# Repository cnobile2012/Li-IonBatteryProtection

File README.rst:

*************************
Li-Ion Battery Protection
*************************
The MIT License (MIT)

This is an electronics project to help protect Li-Ion batteries and the
circuits they are used in. The circuit will work with two to four cells and
protects the battery at the cell level. Any one cell that goes below the
recomended level will cause the entire curcuit to shut down.

=======
LTspice
=======

Spice files for testing the circuit virtually.

Truth Table One: Battery Voltage Normal

+-------+-------+-------+-------+-------+
| U1/U3 | Q1/Q2 | U2/U4 |  Q3   |  Q4   |
+=======+=======+=======+=======+=======+
|  HI   |  LOW  |  LOW  |  HI   |  LOW  |
+-------+-------+-------+-------+-------+
|  N/A  |  ON   |  ON   |  OFF  |  ON   |
+-------+-------+-------+-------+-------+

Truth Table Two: Battery Voltage Below Normal

+-------+-------+-------+-------+-------+
| U1/U3 | Q1/Q2 | U2/U4 |  Q3   |  Q4   |
+=======+=======+=======+=======+=======+
|  LOW  |  HI   |  HI   |  LOW  |  HI   |
+-------+-------+-------+-------+-------+
|  N/A  |  OFF  |  OFF  |  ON   |  OFF  |
+-------+-------+-------+-------+-------+

=====
KiCAD
=====

KiCAD files of the schematic and PCB.

Feel free to contact me at: carl dot nobile at gmail.com

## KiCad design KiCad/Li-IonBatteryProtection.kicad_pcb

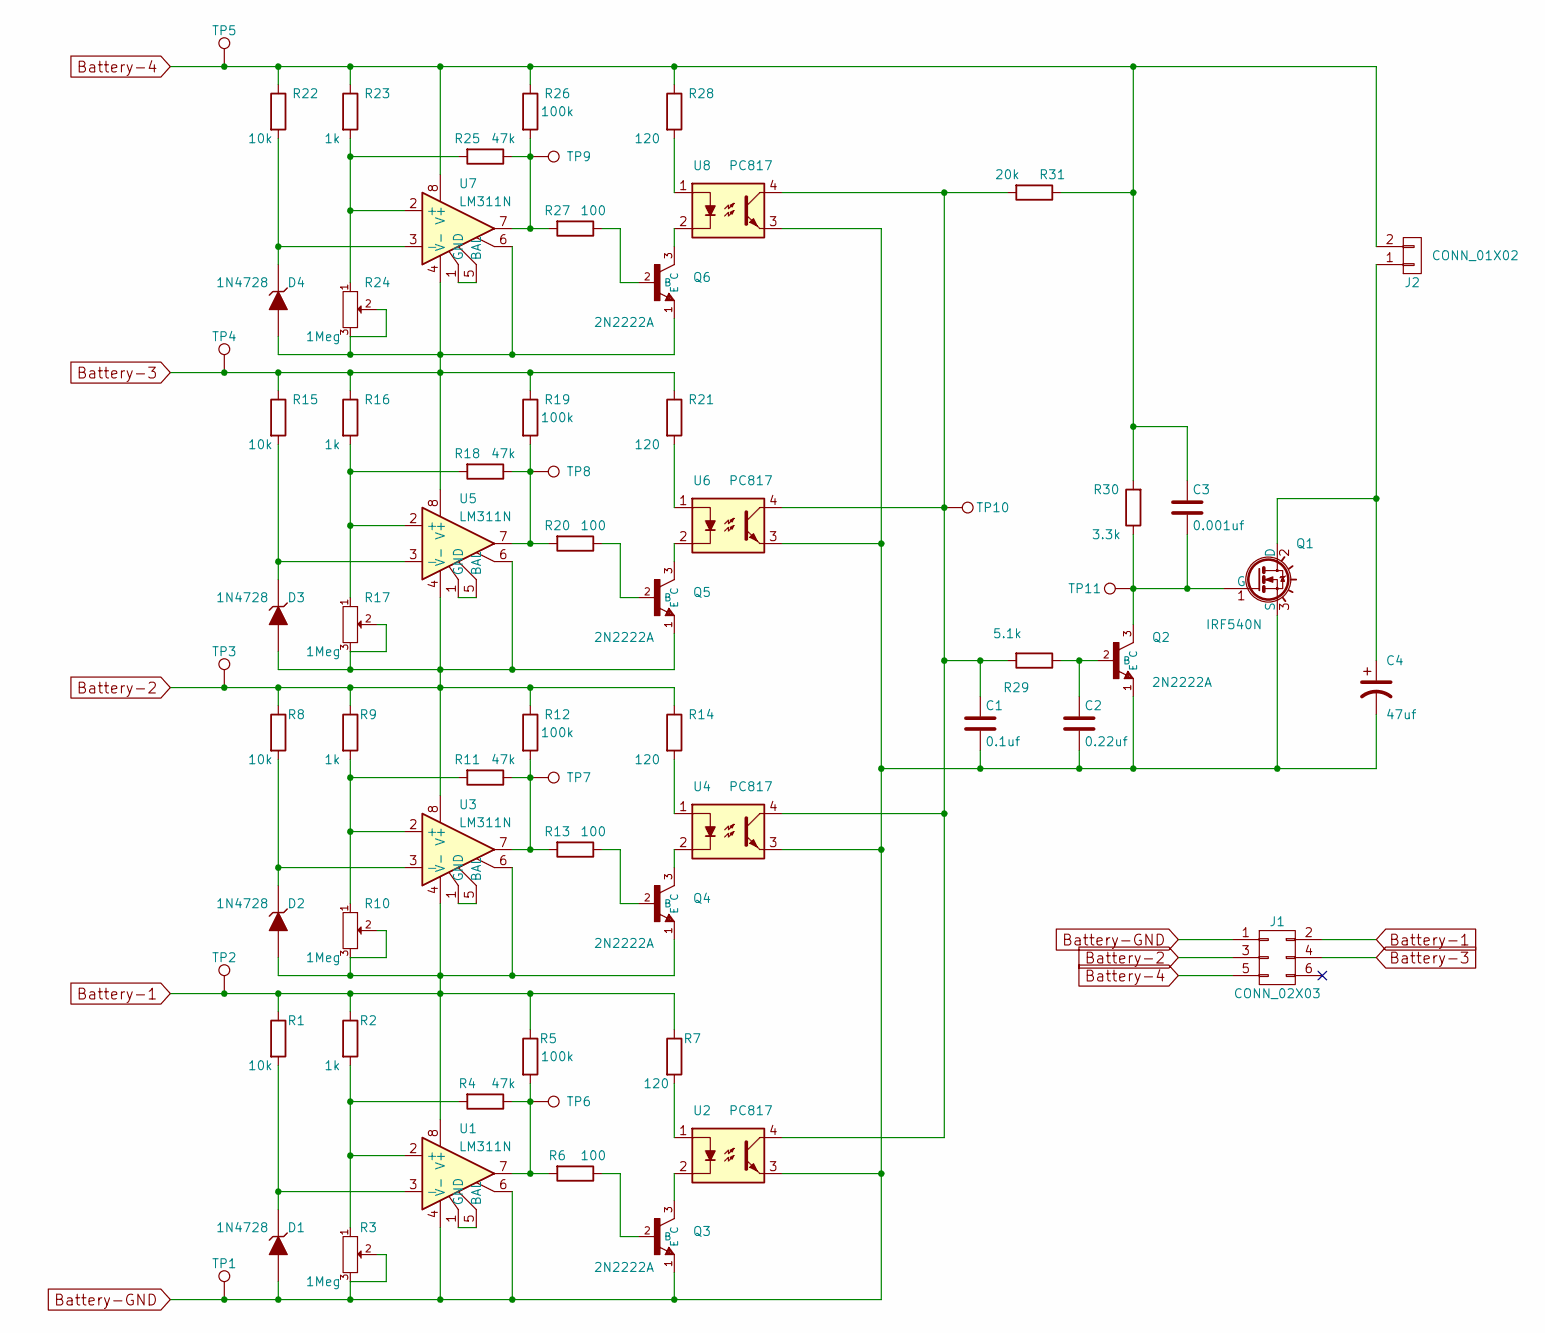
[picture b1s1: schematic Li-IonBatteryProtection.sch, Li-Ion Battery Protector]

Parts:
C1: 0.1uf; C_Rect_L4_W2.5_P2.5
C2: 0.22uf; C_Rect_L7_W2_P5
C3: 0.001uf; C_Rect_L7_W2_P5
C4: 47uf; C_Radial_D5_L11_P2.5
D1, D2, D3, D4: 1N4728; Diode_DO-41_SOD81_Horizontal_RM10
J1: CONN_02X03; Pin_Header_Straight_2x03
J2: CONN_01X02; TerminalBlock_Pheonix_MKDS1.5-2pol
Q1: IRF540N; TO-220_Neutral123_Horizontal
Q2, Q3, Q4, Q5, Q6: 2N2222A; TO-18_3Pin
R1, R8, R15, R22: 10k; Resistor_Horizontal_RM10mm
R2, R9, R16, R23: 1k; Resistor_Horizontal_RM10mm
R3, R10, R17, R24: 1Meg; Potentiometer_Bourns_3296Y_3-8Zoll_Angular_ScrewUp
R4, R11, R18, R25: 47k; Resistor_Horizontal_RM10mm
R5, R12, R19, R26: 100k; Resistor_Horizontal_RM10mm
R6, R13, R20, R27: 100; Resistor_Horizontal_RM10mm
R7, R14, R21, R28: 120; Resistor_Horizontal_RM10mm
R29: 5.1k; Resistor_Horizontal_RM10mm
R30: 3.3k; Resistor_Horizontal_RM10mm
R31: 20k; Resistor_Horizontal_RM10mm
TP1, TP2, TP3, TP4, TP5, TP6, TP7, TP8, TP9, TP10, TP11: TEST_1P; Measurement_Point_Round-TH_Small
U1, U3, U5, U7: LM311N; DIP-8_W7.62mm
U2, U4, U6, U8: PC817; DIP-4_W7.62mm

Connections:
Battery-1: D2.2 (A), J1.2, Q4.1 (E), R1.1, R2.1, R5.1, R7.1, R10.2, R10.3, TP2.1, U1.8 (V+), U3.4 (V-), U3.6
Battery-2: D3.2 (A), J1.3, Q5.1 (E), R8.1, R9.1, R12.1, R14.1, R17.2, R17.3, TP3.1, U3.8 (V+), U5.4 (V-), U5.6
Battery-3: D4.2 (A), J1.4, Q6.1 (E), R15.1, R16.1, R19.1, R21.1, R24.2, R24.3, TP4.1, U5.8 (V+), U7.4 (V-), U7.6
Battery-4: C3.1, J1.5, J2.2, R22.1, R23.1, R26.1, R28.1, R30.2, R31.1, TP5.1, U7.8 (V+)
Battery-GND: C1.2, C2.2, C4.2, D1.2 (A), J1.1, Q1.3 (S), Q2.1 (E), Q3.1 (E), R3.2, R3.3, TP1.1, U1.4 (V-), U1.6, U2.3, U4.3, U6.3, U8.3
unnamed: C1.1, R29.2, R31.2, TP10.1, U2.4, U4.4, U6.4, U8.4
unnamed: C2.1, Q2.2 (B), R29.1
unnamed: C3.2, Q1.1 (G), Q2.3 (C), R30.1, TP11.1
unnamed: C4.1, J2.1, Q1.2 (D)
unnamed: D1.1 (K), R1.2, U1.3 (-)
unnamed: D2.1 (K), R8.2, U3.3 (-)
unnamed: D3.1 (K), R15.2, U5.3 (-)
unnamed: D4.1 (K), R22.2, U7.3 (-)
unnamed: Q3.2 (B), R6.1
unnamed: Q3.3 (C), U2.2
unnamed: Q4.2 (B), R13.1
unnamed: Q4.3 (C), U4.2
unnamed: Q5.2 (B), R20.1
unnamed: Q5.3 (C), U6.2
unnamed: Q6.2 (B), R27.1
unnamed: Q6.3 (C), U8.2
unnamed: R2.2, R3.1, R4.2, U1.2 (+)
unnamed: R4.1, R5.2, R6.2, TP6.1, U1.7
unnamed: R7.2, U2.1
unnamed: R9.2, R10.1, R11.2, U3.2 (+)
unnamed: R11.1, R12.2, R13.2, TP7.1, U3.7
unnamed: R14.2, U4.1
unnamed: R16.2, R17.1, R18.2, U5.2 (+)
unnamed: R18.1, R19.2, R20.2, TP8.1, U5.7
unnamed: R21.2, U6.1
unnamed: R23.2, R24.1, R25.2, U7.2 (+)
unnamed: R25.1, R26.2, R27.2, TP9.1, U7.7
unnamed: R28.2, U8.1
unnamed: U1.1 (GND), U1.5 (BAL)
unnamed: U3.1 (GND), U3.5 (BAL)
unnamed: U5.1 (GND), U5.5 (BAL)
unnamed: U7.1 (GND), U7.5 (BAL)

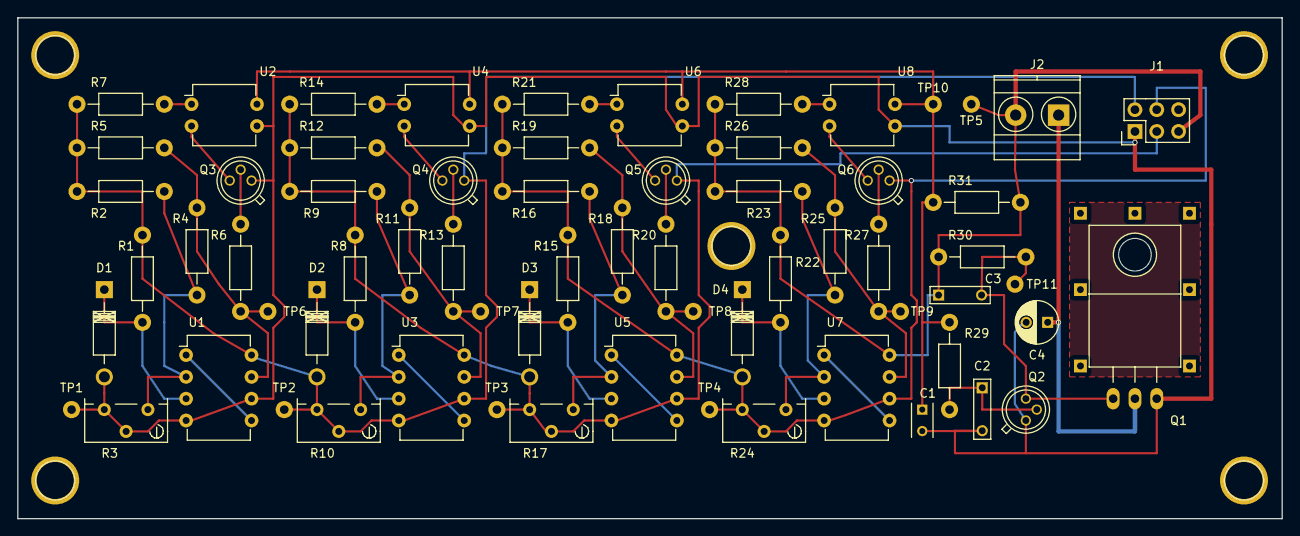
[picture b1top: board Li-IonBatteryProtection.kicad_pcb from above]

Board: 2 copper layers, 147.2 x 58.3 mm, 69 parts (0 on the bottom side), 37 nets.

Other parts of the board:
W5, W7, W8: TEST_1P; Measurement_Point_Round-TH_Big

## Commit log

2017-06-23 Initial commit.
2017-06-25 Net wiring on PCB is done.
2017-06-25 Removed backup files from repo.
2017-06-26 Updated the PDB layout.
2017-06-27 Updated the TO-220 footprint. Started fill zones.
2017-06-28 Updated to the PCB.
2017-07-01 Hopefully finished the PCB.
2017-07-01 Added test points to the schematic.
2017-07-01 Updated the source files.
2017-07-01 Added gerber files.
2017-07-02 Updated the gerber files.
2017-07-19 Moved the Makefile.
2017-07-19 Moved J1 to give more distance between the shroud and the mounting hole.
2017-07-23 Updates to the LTSpice files.
2017-07-23 Update to the RADME.
2017-07-24 Cleaned up the include list.
2017-08-22 Updated the LTSpice files and the README.
2017-08-25 Added the remaining two battery circuits.
2017-10-07 Added diodes to prevent reverse biasing of the comparitors.
2017-10-07 Removed autogenerated files.
2017-10-07 Added autogenerated files to the .gitignore file.
2017-10-07 Updated .gitignore file again and removed a *.plt.
